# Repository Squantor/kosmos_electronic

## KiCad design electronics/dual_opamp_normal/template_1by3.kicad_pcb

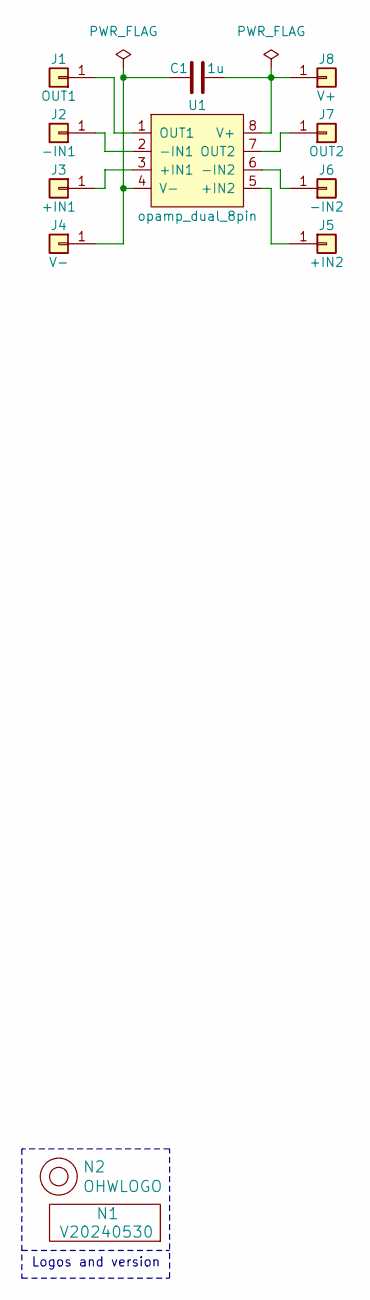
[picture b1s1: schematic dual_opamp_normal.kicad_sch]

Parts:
C1: 1u; C-050-050X100-0805-3516-film
J1: OUT1; PC_pin_nail_head_6092
J2: -IN1; PC_pin_nail_head_6092
J3: +IN1; PC_pin_nail_head_6092
J4: V-; PC_pin_nail_head_6092
J5: +IN2; PC_pin_nail_head_6092
J6: -IN2; PC_pin_nail_head_6092
J7: OUT2; PC_pin_nail_head_6092
J8: V+; PC_pin_nail_head_6092
N1: V20240530; Label_Generic
N2: OHWLOGO; OSHW-Symbol_6.7x6mm_SilkScreen
U1: opamp_dual_8pin; DIP-8_W7.62mm_Socket

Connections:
unnamed: J1.1, U1.1 (OUT1)
unnamed: J2.1, U1.2 (-IN1)
unnamed: J3.1, U1.3 (+IN1)
unnamed: C1.1, J4.1, U1.4 (V-)
unnamed: J5.1, U1.5 (+IN2)
unnamed: J6.1, U1.6 (-IN2)
unnamed: J7.1, U1.7 (OUT2)
unnamed: C1.2, J8.1, U1.8 (V+)

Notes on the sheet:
Logos and version

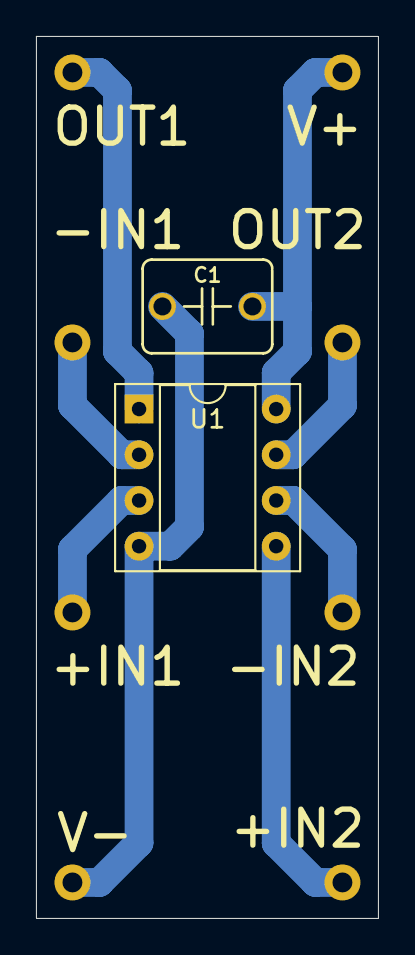
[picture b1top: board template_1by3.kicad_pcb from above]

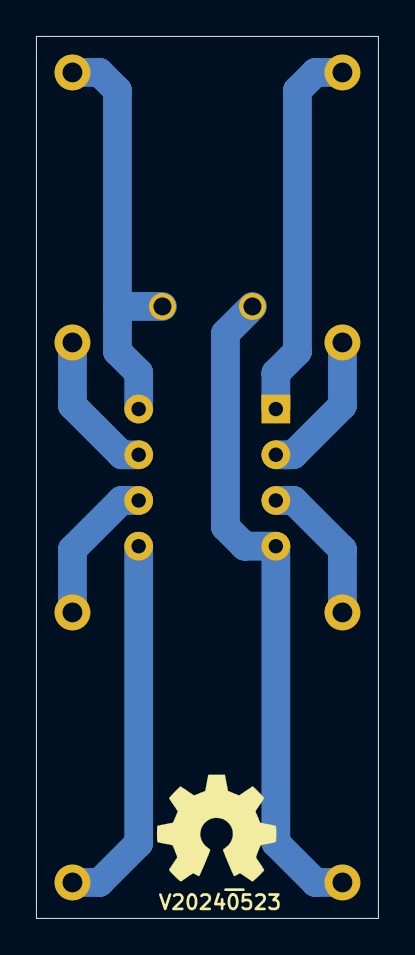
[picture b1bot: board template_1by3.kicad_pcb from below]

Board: 2 copper layers, 19.0 x 49.0 mm, 12 parts (2 on the bottom side), 8 nets.

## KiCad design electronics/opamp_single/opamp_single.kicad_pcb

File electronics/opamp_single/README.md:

# Single opamp module
Single opamp module, fits various opamps that fit the LM741 industry standard pinout.
## BOM
* The X1000 and XN1000 special pins for the connections, I have found something similar by [Mill-max 6092](https://www.mill-max.com/catalog/download/2020-10%3A207M.pdf) available at [digikey](https://www.digikey.com/en/products/detail/mill-max-manufacturing-corp/6092-0-00-15-00-00-33-0/1991698)

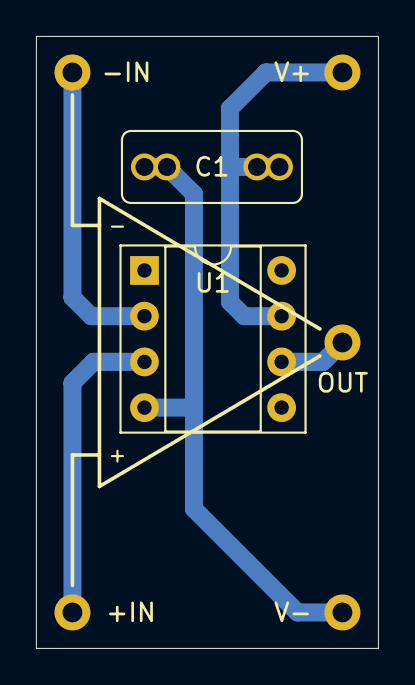
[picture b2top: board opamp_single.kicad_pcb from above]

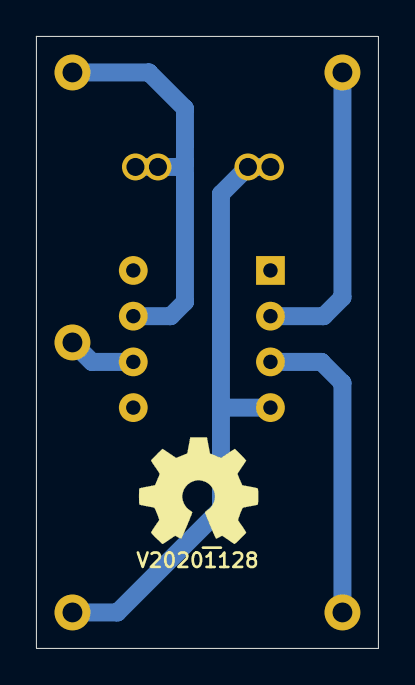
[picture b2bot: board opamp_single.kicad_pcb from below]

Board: 2 copper layers, 19.0 x 34.0 mm, 9 parts (2 on the bottom side), 5 nets.

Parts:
C1: 100n; C-050_075-040X100
J1: -IN; PC_pin_nail_head_6092
J3: +IN; PC_pin_nail_head_6092
J4: V-; PC_pin_nail_head_6092
J5: OUT; PC_pin_nail_head_6092
J6: V+; PC_pin_nail_head_6092
N1: V20201128; Label_Generic
N2: OHWLOGO; OSHW-Symbol_6.7x6mm_SilkScreen
U1: opamp_single_8pin; DIP-8_W7.62mm_Socket

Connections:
/V+: C1.2, J6.1, U1.7
/V-: C1.1, J4.1, U1.4
unnamed: J1.1, U1.2
unnamed: J3.1, U1.3
unnamed: J5.1, U1.6
